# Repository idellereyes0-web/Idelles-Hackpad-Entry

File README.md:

# Idelles-Hackpad-Entry
This is my entry for the hackclub hackpad blueprint! My hackpad is simple and is used to adjust volume, open apps, and to copy/paste. BOM - 4x MX-Style switches, 4x white blank DSA keycaps 1x unsoldered Seeed XIAO RP2040, 1x EC11 Rotary encoder, 2 piece case (top and bottom).

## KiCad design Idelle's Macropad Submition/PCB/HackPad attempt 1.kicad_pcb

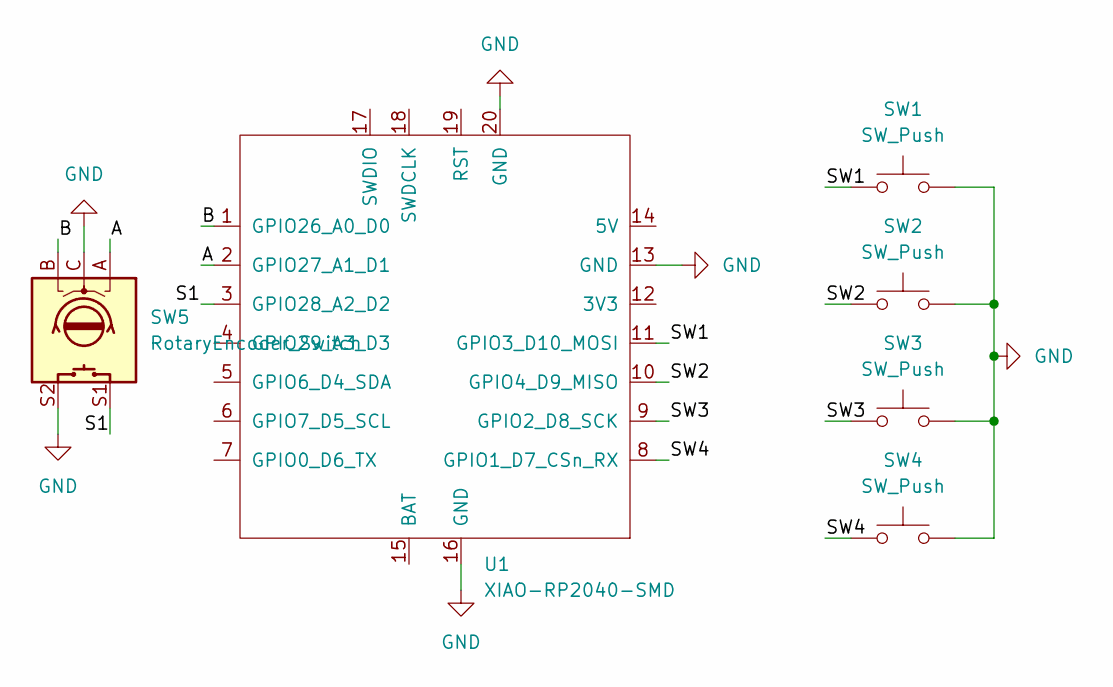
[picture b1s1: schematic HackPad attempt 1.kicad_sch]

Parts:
SW1, SW2, SW3, SW4: SW_Push; SW_Cherry_MX_1.00u_PCB
SW5: RotaryEncoder_Switch; RotaryEncoder_Alps_EC11E-Switch_Vertical_H20mm
U1: XIAO-RP2040-SMD; XIAO-RP2040-SMD (1)

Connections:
/A: SW5.A, U1.2 (GPIO27_A1_D1)
/B: SW5.B, U1.1 (GPIO26_A0_D0)
/S1: SW5.S1, U1.3 (GPIO28_A2_D2)
/SW1: SW1.1, U1.11 (GPIO3_D10_MOSI)
/SW2: SW2.1, U1.10 (GPIO4_D9_MISO)
/SW3: SW3.1, U1.9 (GPIO2_D8_SCK)
/SW4: SW4.1, U1.8 (GPIO1_D7_CSn_RX)
GND: SW1.2, SW2.2, SW3.2, SW4.2, SW5.C, SW5.S2, U1.13 (GND), U1.16 (GND), U1.20 (GND)

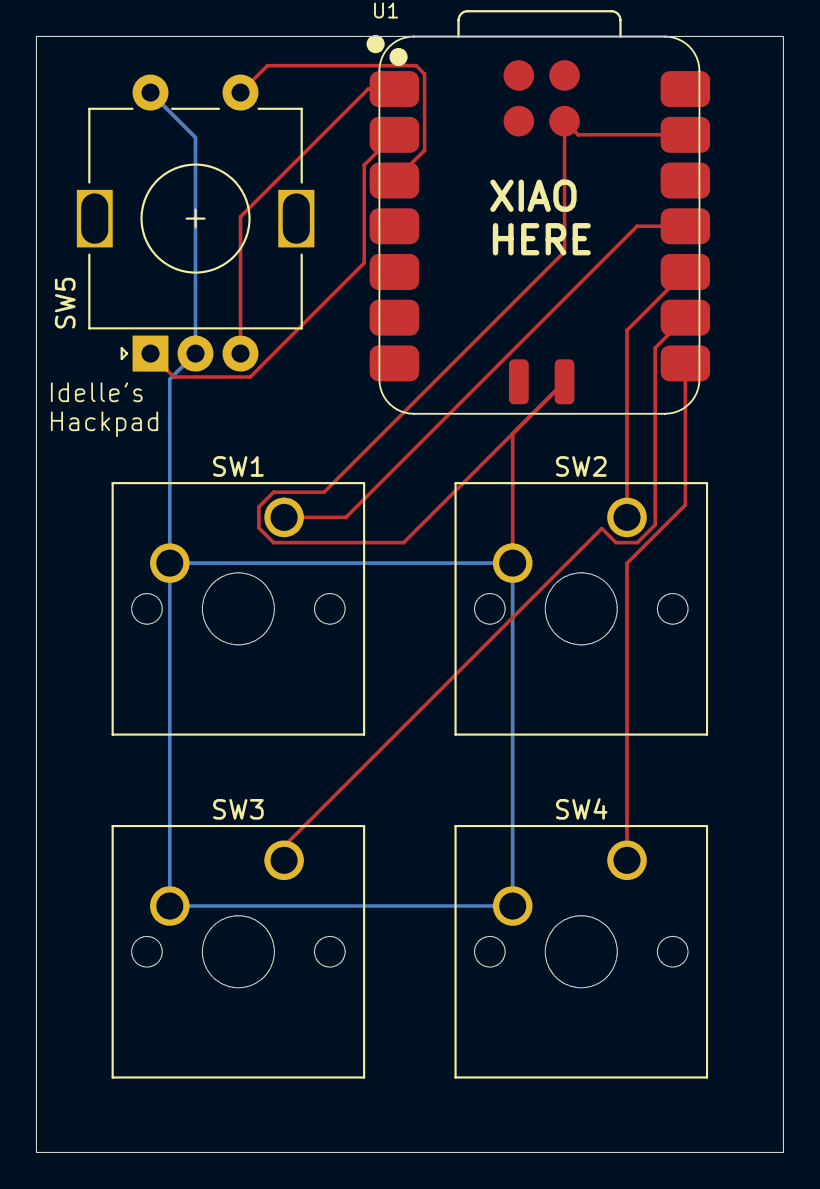
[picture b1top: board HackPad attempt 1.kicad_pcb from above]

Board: 2 copper layers, 41.5 x 62.0 mm, 6 parts (0 on the bottom side), 8 nets.

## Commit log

2026-02-19 Update README with detailed hackpad project description
    Expanded description of the hackpad project with details on components and functionality.
2026-02-19 Revise BOM description in README
    Updated the bill of materials (BOM) to specify two case pieces.
2026-02-19 Add images to README for better visualization
    Added images to enhance the README with visual examples.
